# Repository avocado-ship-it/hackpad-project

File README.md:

# hackpad
i made this not just for highway but because i will get alot of use out of it. this will be a stream deck esque pc controller using kmk firmware

| QTY | Supplies |
|-----|----------|
| 1 | Seed Studio XIAO RP2040 |
| 5 | MX-Style Switches |
| 4 | Keycaps |
| 1 | 3D Printed Case(top) |
| 1 | 3D Printed Case(bottom) |
| 1 | PCB |
| 1 | Soldering Iron |
| 1 | Spool of Solder |

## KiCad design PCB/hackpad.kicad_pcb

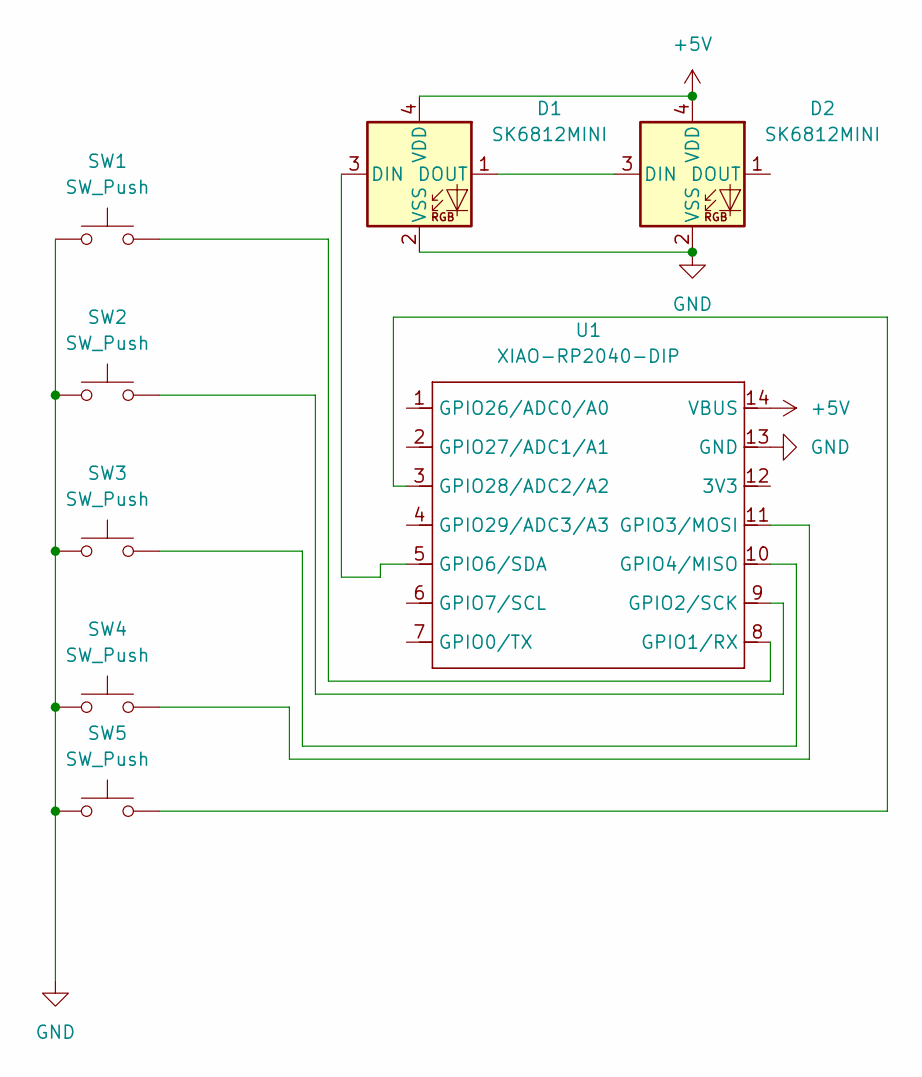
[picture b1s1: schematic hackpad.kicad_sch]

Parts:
D1, D2: SK6812MINI; LED_SK6812MINI_PLCC4_3.5x3.5mm_P1.75mm
SW1, SW2, SW3, SW4, SW5: SW_Push; SW_Cherry_MX_1.00u_PCB
U1: XIAO-RP2040-DIP

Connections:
+5V: D1.4 (VDD), D2.4 (VDD), U1.14 (VBUS)
GND: D1.2 (VSS), D2.2 (VSS), SW1.1, SW2.1, SW3.1, SW4.1, SW5.1, U1.13 (GND)
unnamed: D1.3 (DIN), U1.5 (GPIO6/SDA)
unnamed: D1.1 (DOUT), D2.3 (DIN)
unnamed: SW1.2, U1.8 (GPIO1/RX)
unnamed: SW2.2, U1.9 (GPIO2/SCK)
unnamed: SW4.2, U1.11 (GPIO3/MOSI)
unnamed: SW3.2, U1.10 (GPIO4/MISO)
unnamed: SW5.2, U1.3 (GPIO28/ADC2/A2)

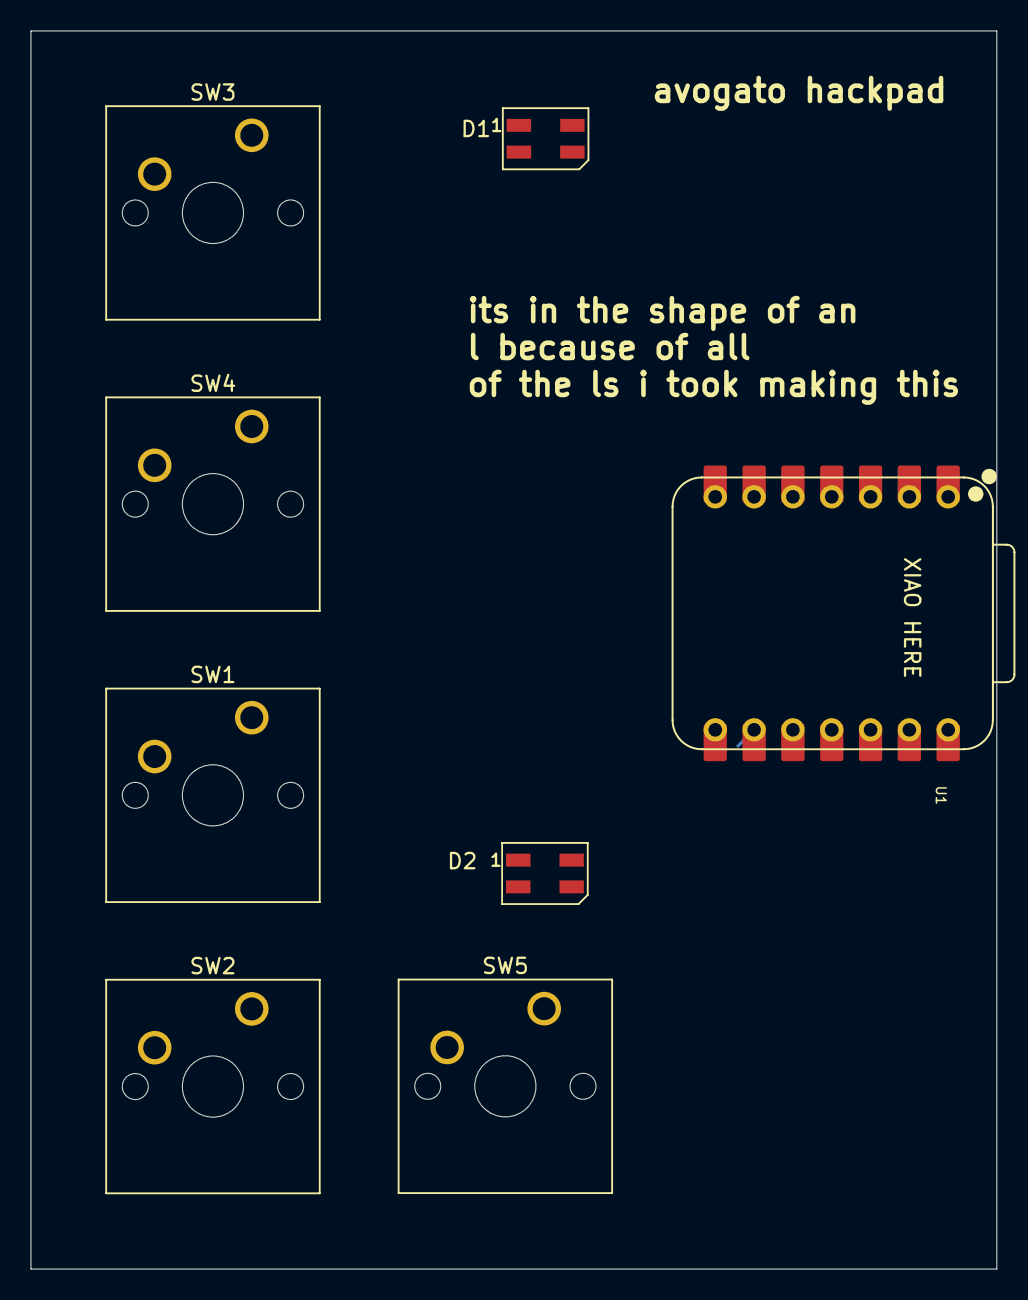
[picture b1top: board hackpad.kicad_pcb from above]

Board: 2 copper layers, 63.2 x 81.0 mm, 8 parts (0 on the bottom side), 9 nets.

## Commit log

2025-06-29 updated grbr
2025-07-07 updated to be submitable
2025-07-08 moved grbr files to zip and added drl
2025-07-08 added step
2025-07-08 added to proper folder
